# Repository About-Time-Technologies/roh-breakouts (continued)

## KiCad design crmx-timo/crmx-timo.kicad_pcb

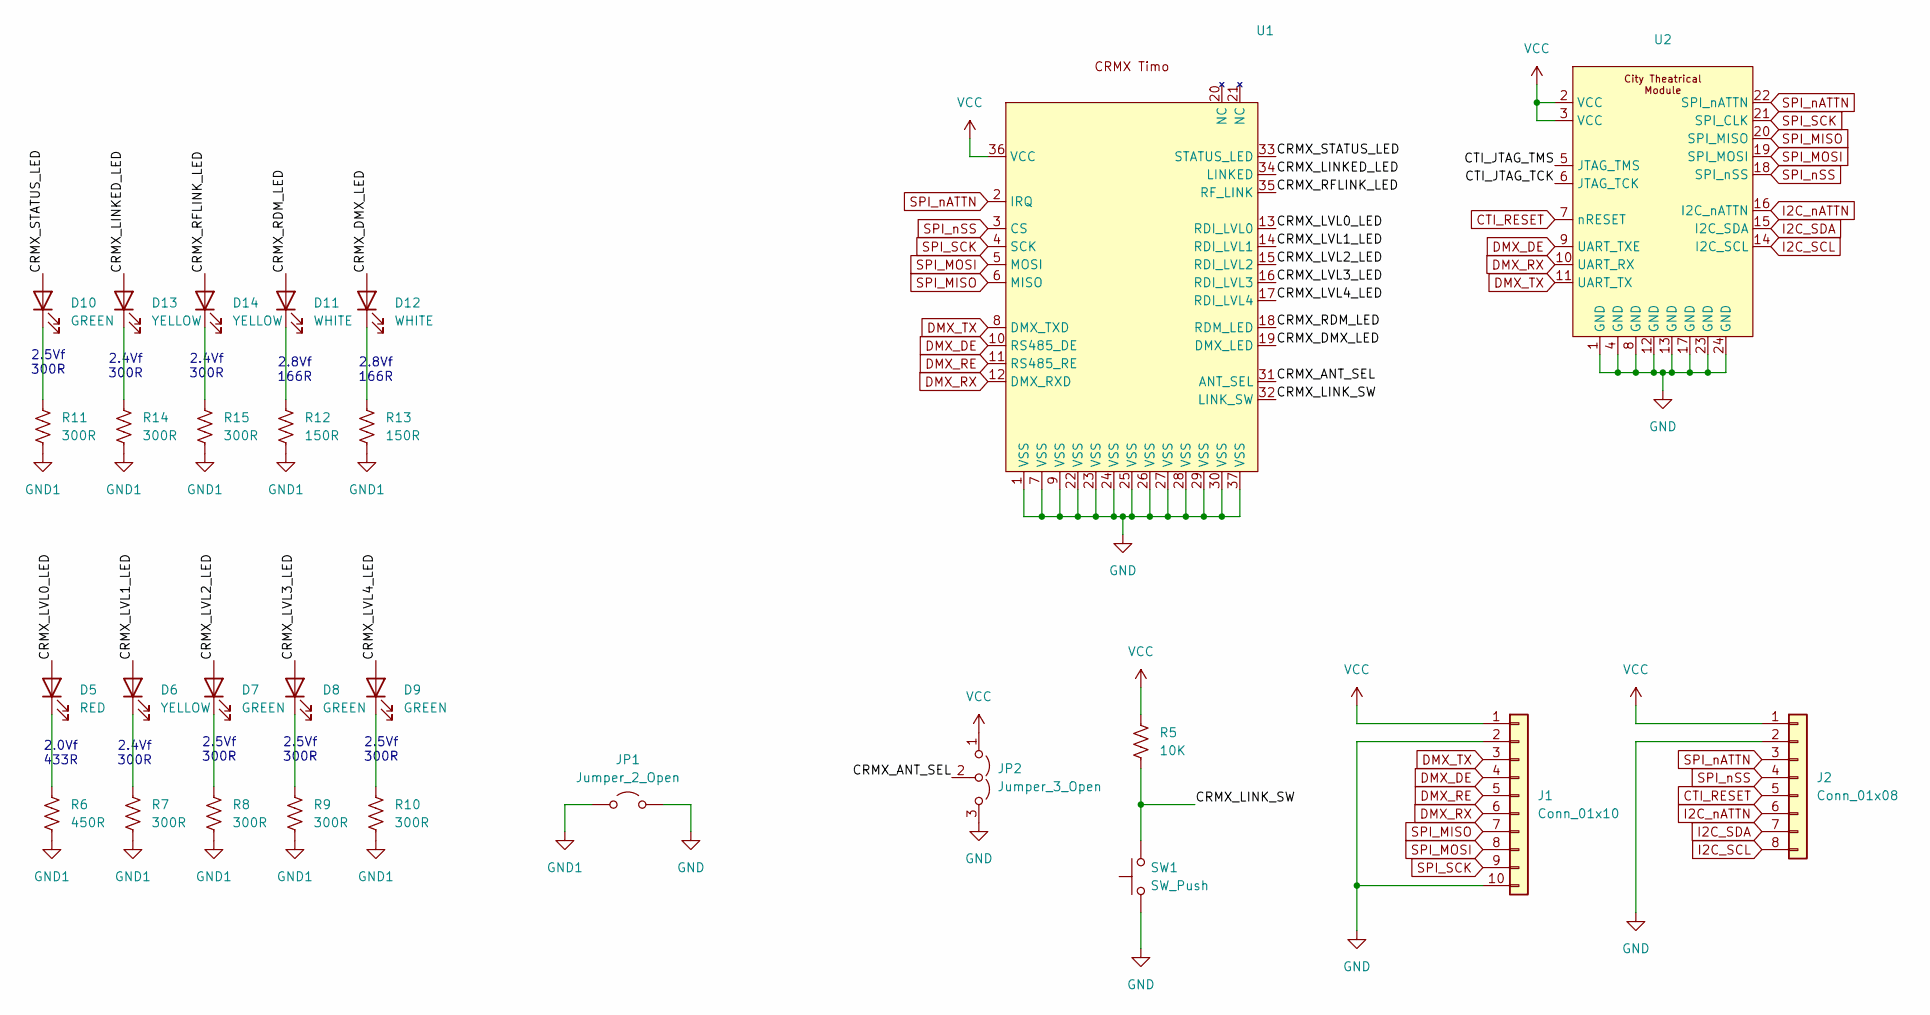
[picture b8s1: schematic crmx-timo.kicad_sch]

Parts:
D5: RED; LED_0603_1608Metric; LCSC C2286
D6, D13, D14: YELLOW; LED_0603_1608Metric; LCSC C72038
D7, D8, D9, D10: GREEN; LED_0603_1608Metric
D11, D12: WHITE; LED_0603_1608Metric; LCSC C2290
J1: Conn_01x10; PinHeader_1x10_P2.54mm_Vertical
J2: Conn_01x08; PinHeader_1x08_P2.54mm_Vertical
JP1: Jumper_2_Open; SolderJumper-2_P1.3mm_Open_RoundedPad1.0x1.5mm
JP2: Jumper_3_Open; SolderJumper-3_P1.3mm_Open_RoundedPad1.0x1.5mm
R5: 10K; R_0603_1608Metric; LCSC C25804
R6: 450R; R_0603_1608Metric; LCSC C23170
R7, R8, R9, R10, R11, R14, R15: 300R; R_0603_1608Metric; LCSC C23025
R12, R13: 150R; R_0603_1608Metric; LCSC C22808
SW1: SW_Push; SW_Tactile_SPST_NO_Straight_CK_PTS636Sx25SMTRLFS
U1: CRMX-TiMo
U2: CTI-5994

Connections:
/CRMX_ANT_SEL: JP2.2 (C), U1.31 (ANT_SEL)
/CRMX_DMX_LED: D12.2 (A), U1.19 (DMX_LED)
/CRMX_LINKED_LED: D13.2 (A), U1.34 (LINKED)
/CRMX_LINK_SW: R5.2, SW1.2, U1.32 (LINK_SW)
/CRMX_LVL0_LED: D5.2 (A), U1.13 (RDI_LVL0)
/CRMX_LVL1_LED: D6.2 (A), U1.14 (RDI_LVL1)
/CRMX_LVL2_LED: D7.2 (A), U1.15 (RDI_LVL2)
/CRMX_LVL3_LED: D8.2 (A), U1.16 (RDI_LVL3)
/CRMX_LVL4_LED: D9.2 (A), U1.17 (RDI_LVL4)
/CRMX_RDM_LED: D11.2 (A), U1.18 (RDM_LED)
/CRMX_RFLINK_LED: D14.2 (A), U1.35 (RF_LINK)
/CRMX_STATUS_LED: D10.2 (A), U1.33 (STATUS_LED)
CTI_RESET: J2.5, U2.7 (nRESET)
DMX_DE: J1.4, U1.10 (RS485_DE), U2.9 (UART_TXE)
DMX_RE: J1.5, U1.11 (RS485_RE)
DMX_RX: J1.6, U1.12 (DMX_RXD), U2.10 (UART_RX)
DMX_TX: J1.3, U1.8 (DMX_TXD), U2.11 (UART_TX)
GND: J1.2, J1.10, J2.2, JP1.2 (B), JP2.3 (B), SW1.1, U1.1 (VSS), U1.7 (VSS), U1.9 (VSS), U1.22 (VSS), U1.23 (VSS), U1.24 (VSS), U1.25 (VSS), U1.26 (VSS), U1.27 (VSS), U1.28 (VSS), U1.29 (VSS), U1.30 (VSS), U1.37 (VSS), U2.1 (GND), U2.4 (GND), U2.8 (GND), U2.12 (GND), U2.13 (GND), U2.17 (GND), U2.23 (GND), U2.24 (GND)
GND1: JP1.1 (A), R6.2, R7.2, R8.2, R9.2, R10.2, R11.2, R12.2, R13.2, R14.2, R15.2
I2C_SCL: J2.8, U2.14 (I2C_SCL)
I2C_SDA: J2.7, U2.15 (I2C_SDA)
I2C_nATTN: J2.6, U2.16 (I2C_nATTN)
unnamed: D5.1 (K), R6.1
unnamed: D6.1 (K), R7.1
unnamed: D7.1 (K), R8.1
unnamed: D8.1 (K), R9.1
unnamed: D9.1 (K), R10.1
unnamed: D10.1 (K), R11.1
unnamed: D11.1 (K), R12.1
unnamed: D12.1 (K), R13.1
unnamed: D13.1 (K), R14.1
unnamed: D14.1 (K), R15.1
SPI_MISO: J1.7, U1.6 (MISO), U2.20 (SPI_MISO)
SPI_MOSI: J1.8, U1.5 (MOSI), U2.19 (SPI_MOSI)
SPI_SCK: J1.9, U1.4 (SCK), U2.21 (SPI_CLK)
SPI_nATTN: J2.3, U1.2 (IRQ), U2.22 (SPI_nATTN)
SPI_nSS: J2.4, U1.3 (CS), U2.18 (SPI_nSS)
VCC: J1.1, J2.1, JP2.1 (A), R5.1, U1.36 (VCC), U2.2 (VCC), U2.3 (VCC)

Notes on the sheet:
2.0Vf 433R
2.5Vf 300R
2.8Vf 166R
2.4Vf 300R

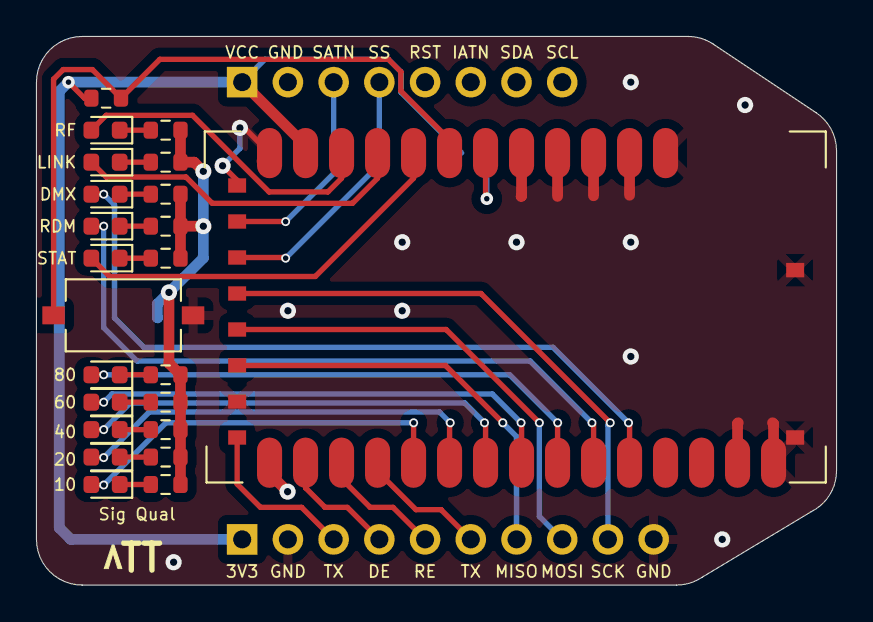
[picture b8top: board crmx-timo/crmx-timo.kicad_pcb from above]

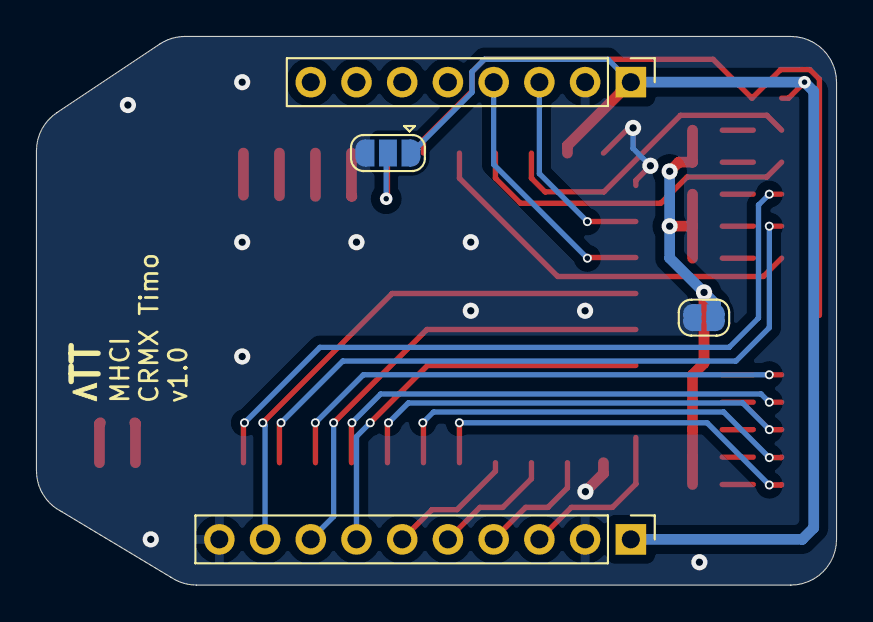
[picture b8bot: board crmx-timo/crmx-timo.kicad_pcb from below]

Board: 2 copper layers, 44.5 x 30.5 mm, 27 parts (4 on the bottom side), 34 nets.

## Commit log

2024-08-30 Isolated RS485 breakout board
2024-08-30 24v 4A boost board - schematic ready
2024-11-20 Added isolated voltage regulator to RS485 board
2024-11-20 ADM2486 Breakout board
2024-12-27 A6211 Basic Layout
2024-12-31 Timo CRMX Breakout
2025-01-03 A6211 - Adding comments from Tommy
2025-01-03 CRMX-Timo Production files
2025-01-05 MV-5449 board
2025-01-05 Logos and description
2025-01-05 ISO DMX Logos
2025-01-05 v1 Production Files
2025-01-13 A6211 Routing and Layout Completed
2025-01-14 A6211 Production v1
2025-01-25 Walkure motherboard initial scope
2025-01-29 Walkure motherboard v1.0 schematic
2025-01-29 Adding fans and breakouts
2025-01-30 Walkure motherboard production v1.0
2025-02-11 A6211 BOM files
2025-03-10 Make GND connections use spokes to reduce soldering issues
2025-03-15 TPS922055 initial schematic
2025-03-15 Cheaper diode
2025-03-15 Schematic needs vias
2025-03-17 TPS Layout complete
2025-03-17 A6211 JLCPCB reference
2025-03-17 A6211 v1.1
2025-03-18 A6211 - cheaper inductor
2025-03-18 TPS922052 - Larger inductor
2025-03-22 Update Tset value to 120 degC
2025-03-23 TPS922052 v1.0
2025-03-27 Auto stash before merge of "1.1" and "origin/1.1"
2025-03-27 Auto stash before merge of "main" and "origin/main"
2025-04-08 Motherboard production src
